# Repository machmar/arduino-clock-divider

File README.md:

# arduino-clock-divider
A clock divider that uses a arduino. It divides by 1; 2; 3; 4; 5; 6; 7; 8; 9 and 10.
```
Animations: (only some versions have this feature - the 1.1.1 and 1.4.1 dont have it for sure and Im not sure about the other versions)
       1.Activate them by unplugging the clock source.
       2.Use the divide by 10 as a clock input for animations.
       3.To select animations, Send a trigger to the divide by 9 pin.
       4.All of the animations are displayed on the divide by 1 to 8 leds
       5.Even thought it is displaying animations, it is still sending gates.
       6.To get back to dividing, just plug the clock jack back in.
```
THIS DIVIDER WILL NOT WORK WITH STEREO CABLES, as it relies on the fact that the mono jack shorts the second terminal of the stereo jack to ground. So If you want to make it work with stereo cables, than you have to connect the second contact to ground on the other side of the cable.

TO MAKE THIS WORK WITH STEREO CABLES, you just need to connect pin A0 to ground. That way the arduino will think you have a jack connected all the time, thus not deploing any animations at all. A optional thing you can do is to add a switch to the A0 that swithecs between 5 and 0 Volts.

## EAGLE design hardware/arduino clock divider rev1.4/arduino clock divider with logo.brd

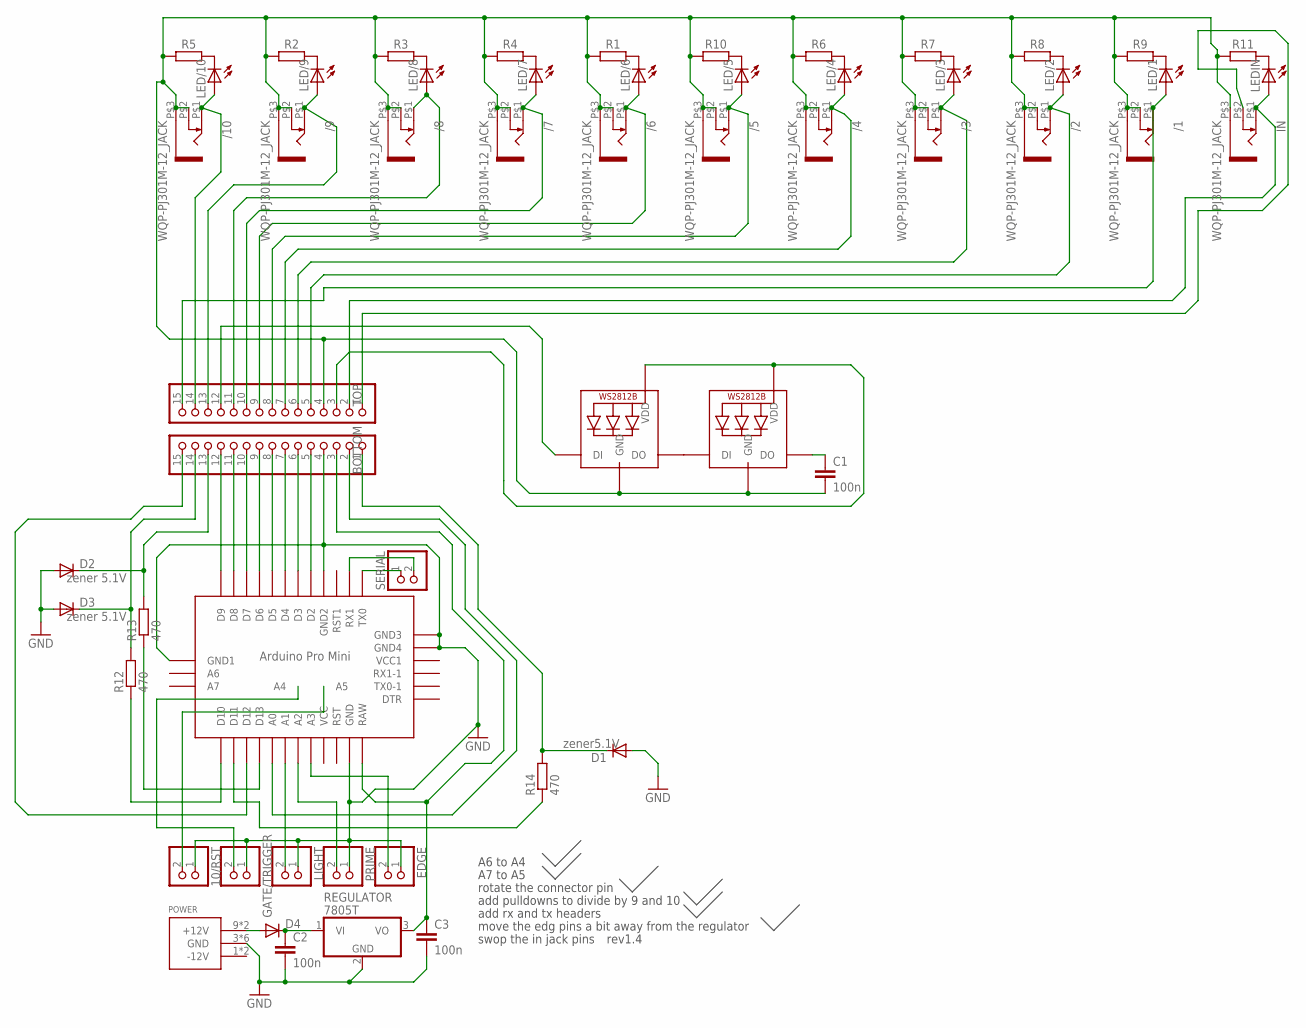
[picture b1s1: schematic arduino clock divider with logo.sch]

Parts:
10/RST: PINHD-1X2; 1X02
/1, /2, /3, /4, /5, /6, /7, /8, /9, /10: WQP-PJ301M-12_JACK
BOTTOM: PINHD-1X15-CB; 1X15-CB3D
C1, C2, C3: 100n; C025-025X050
D1: zener5.1V; DO35-10
D2, D3: zener 5.1V; DO35-10
D4: BAV21; DO35-10
EDGE: PINHD-1X2; 1X02
GATE/TRIGGER: PINHD-1X2; 1X02
IN: WQP-PJ301M-12_JACK
LED/1, LED/2, LED/3, LED/4, LED/5, LED/6, LED/7, LED/8, LED/9, LED/10: LED3MM
LEDIN: LED3MM
LIGHT: PINHD-1X2; 1X02
NEOPIX1, NEOPIX2: WS2812B5050; WS2812B
POWER: POWER_SIMPLE10; POWER_10
PRIME: PINHD-1X2; 1X02
R1, R2, R3, R4, R5, R6, R7, R8, R9, R10: 1k; 0204V
R11: 330; 0204V
R12, R13, R14: 470; 0204/7
REGULATOR: 7805T; TO220H
SERIAL: PINHD-1X2; 1X02
TOP: PINHD-1X15-CB; 1X15-CB3D
U$1: ABK-PRO-MINI-SMD

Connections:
GND: 10/RST.1, BOTTOM.4, C2.2, C3.2, D1.A, D2.A, D3.A, EDGE.1, GATE/TRIGGER.1, LIGHT.1, POWER.3 (GND), POWER.4 (GND), POWER.5 (GND), POWER.6 (GND), POWER.7 (GND), POWER.8 (GND), PRIME.1, REGULATOR.2 (GND), U$1.GND, U$1.GND1, U$1.GND2, U$1.GND3, U$1.GND4
unnamed: /6.P$1 (2), LED/6.A, TOP.9
unnamed: LED/6.K (C), R1.2
unnamed: BOTTOM.13, D2.C, R13.2
unnamed: LED/9.K (C), R2.2
unnamed: /8.P$1 (2), LED/8.A, TOP.11
unnamed: LED/8.K (C), R3.2
unnamed: /5.P$1 (2), LED/5.A, TOP.8
unnamed: LED/7.K (C), R4.2
unnamed: BOTTOM.14, D3.C, R12.2
unnamed: LED/10.K (C), R5.2
unnamed: /4.P$1 (2), LED/4.A, TOP.7
unnamed: LED/4.K (C), R6.2
unnamed: /3.P$1 (2), LED/3.A, TOP.6
unnamed: LED/3.K (C), R7.2
unnamed: /2.P$1 (2), LED/2.A, TOP.5
unnamed: LED/2.K (C), R8.2
unnamed: D4.A, POWER.9 (+12V), POWER.10 (+12V)
unnamed: LED/1.K (C), R9.2
unnamed: C2.1, D4.C, REGULATOR.1 (VI)
unnamed: LED/5.K (C), R10.2
unnamed: R14.1, U$1.D11
unnamed: LEDIN.K (C), R11.2
unnamed: IN.P$2 (3), TOP.1
unnamed: NEOPIX1.4-DIN (DI), TOP.12
unnamed: /7.P$1 (2), LED/7.A, TOP.10
unnamed: NEOPIX1.2-DOUT (DO), NEOPIX2.4-DIN (DI)
unnamed: /10.P$1 (2), LED/10.A, TOP.14
unnamed: C1.1, NEOPIX2.2-DOUT (DO)
unnamed: /9.P$1 (2), LED/9.A, TOP.13
unnamed: NEOPIX1.1-VDD (VDD), NEOPIX2.1-VDD (VDD), TOP.3
unnamed: PRIME.2, U$1.A2
unnamed: BOTTOM.3, C3.1, REGULATOR.3 (VO), U$1.RAW
unnamed: BOTTOM.12, U$1.D9
unnamed: BOTTOM.11, U$1.D8
unnamed: BOTTOM.10, U$1.D7
unnamed: BOTTOM.9, U$1.D6
unnamed: BOTTOM.8, U$1.D5
unnamed: BOTTOM.7, U$1.D4
unnamed: BOTTOM.6, U$1.D3
unnamed: BOTTOM.5, U$1.D2
unnamed: R13.1, U$1.D13
unnamed: R12.1, U$1.D10
unnamed: IN.P$1 (2), LEDIN.A, TOP.2
unnamed: /1.P$1 (2), LED/1.A, TOP.15
unnamed: BOTTOM.1, D1.C, R14.2
unnamed: BOTTOM.15, U$1.D12
unnamed: LIGHT.2, U$1.A1
unnamed: BOTTOM.2, U$1.A0
unnamed: EDGE.2, U$1.A3
unnamed: 10/RST.2, U$1.A5
unnamed: GATE/TRIGGER.2, U$1.A4
unnamed: SERIAL.2, U$1.RX1
unnamed: SERIAL.1, U$1.TX0
TOPGND: /1.P$2 (3), /1.P$3 (1), /2.P$2 (3), /2.P$3 (1), /3.P$2 (3), /3.P$3 (1), /4.P$2 (3), /4.P$3 (1), /5.P$2 (3), /5.P$3 (1), /6.P$2 (3), /6.P$3 (1), /7.P$2 (3), /7.P$3 (1), /8.P$2 (3), /8.P$3 (1), /9.P$2 (3), /9.P$3 (1), /10.P$2 (3), /10.P$3 (1), C1.2, IN.P$3 (1), NEOPIX1.3-GND (GND), NEOPIX2.3-GND (GND), R1.1, R2.1, R3.1, R4.1, R5.1, R6.1, R7.1, R8.1, R9.1, R10.1, R11.1, TOP.4

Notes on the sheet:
A6 to A4
A7 to A5
rotate the connector pin
add pulldowns to divide by 9 and 10
add rx and tx headers
move the edg pins a bit away from the regulator
swop the in jack pins
rev1.4

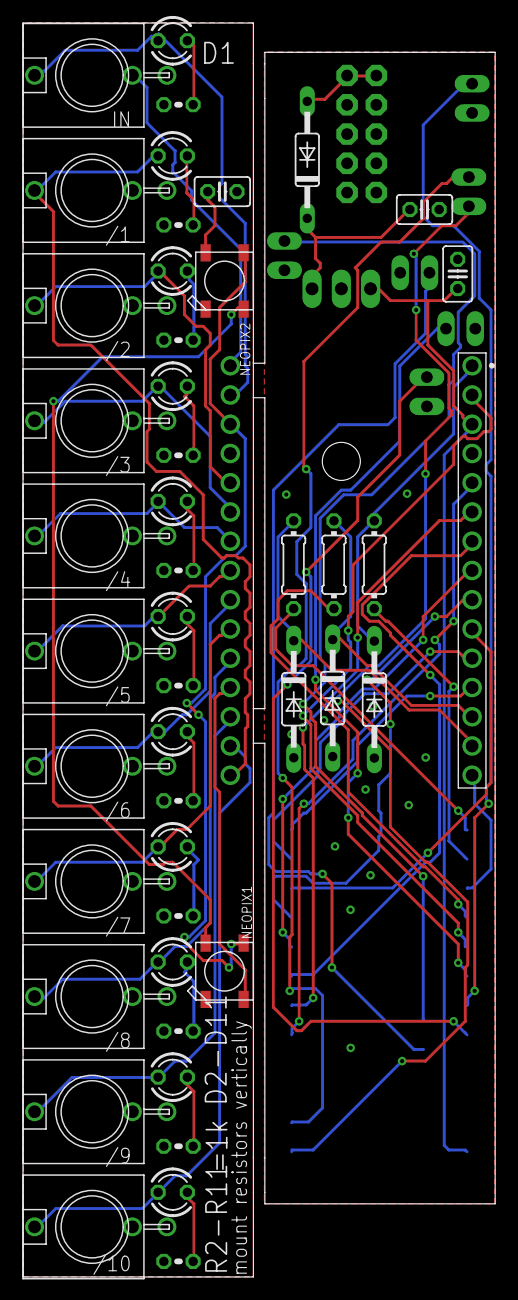
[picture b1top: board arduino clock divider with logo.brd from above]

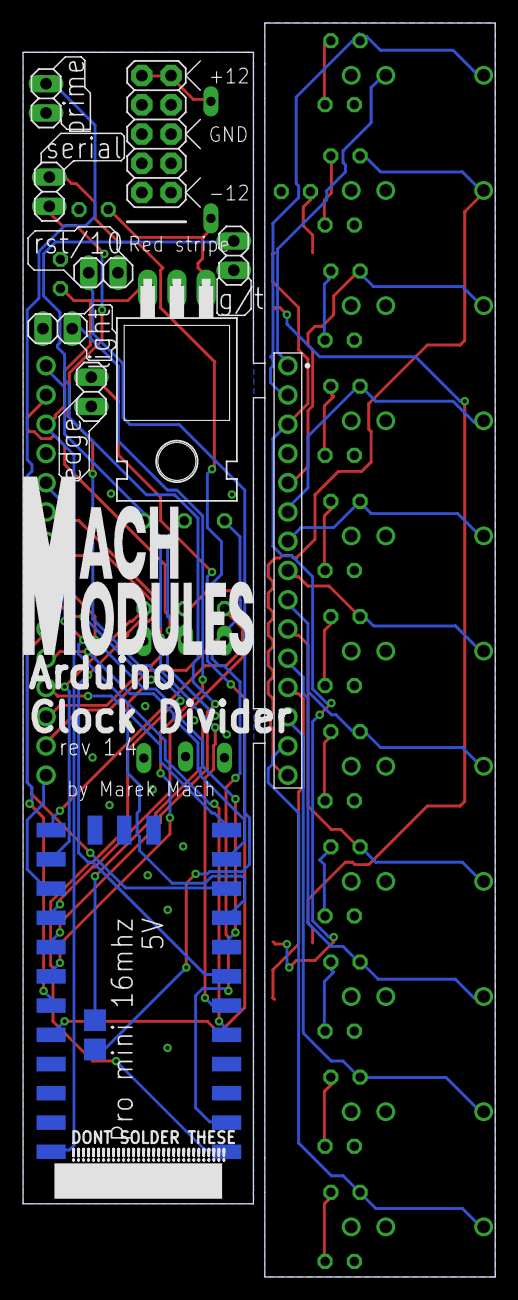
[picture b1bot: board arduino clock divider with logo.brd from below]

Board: 2 copper layers, 41.0 x 108.9 mm, 56 parts (10 on the bottom side), 55 nets.

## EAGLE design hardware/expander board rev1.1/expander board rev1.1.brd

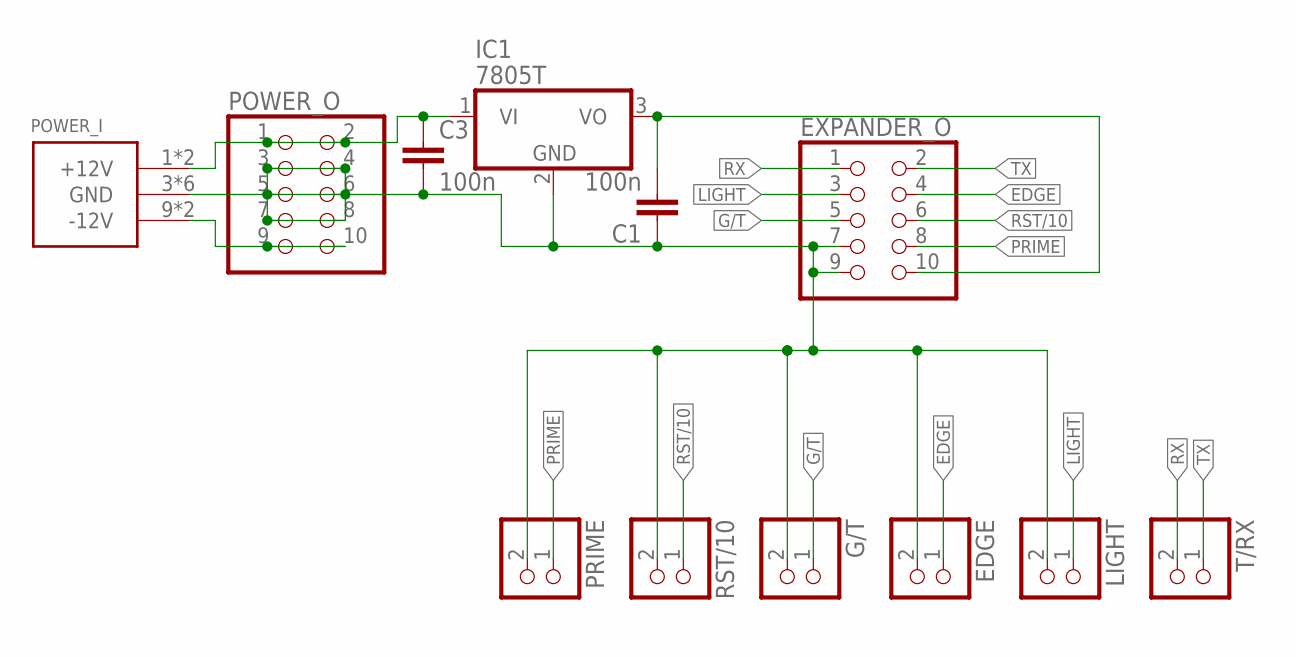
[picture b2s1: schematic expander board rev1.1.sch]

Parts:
C1, C3: 100n; C025-025X050
EDGE: PINHD-1X2; 1X02
EXPANDER_O: PINHD-2X5; 2X05
G/T: PINHD-1X2; 1X02
IC1: 7805T; TO220H
LIGHT: PINHD-1X2; 1X02
POWER_I: POWER_SIMPLE; POWER_10_NSTRIPE
POWER_O: PINHD-2X5; 2X05
PRIME: PINHD-1X2; 1X02
RST/10: PINHD-1X2; 1X02
T/RX: PINHD-1X2; 1X02

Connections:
+5V: C1.2, EXPANDER_O.10, IC1.3 (VO)
+12V: C3.1, IC1.1 (VI), POWER_I.1 (+12V), POWER_I.2 (+12V), POWER_O.1, POWER_O.2
-12V: POWER_I.9 (-12V), POWER_I.10 (-12V), POWER_O.9, POWER_O.10
EDGE: EDGE.1, EXPANDER_O.4
G/T: EXPANDER_O.5, G/T.1
GND: C1.1, C3.2, EDGE.2, EXPANDER_O.7, EXPANDER_O.9, G/T.2, IC1.2 (GND), LIGHT.2, POWER_I.3 (GND), POWER_I.4 (GND), POWER_I.5 (GND), POWER_I.6 (GND), POWER_I.7 (GND), POWER_I.8 (GND), POWER_O.3, POWER_O.4, POWER_O.5, POWER_O.6, POWER_O.7, POWER_O.8, PRIME.2, RST/10.2
LIGHT: EXPANDER_O.3, LIGHT.1
PRIME: EXPANDER_O.8, PRIME.1
RST/10: EXPANDER_O.6, RST/10.1
RX: EXPANDER_O.1, T/RX.2
TX: EXPANDER_O.2, T/RX.1

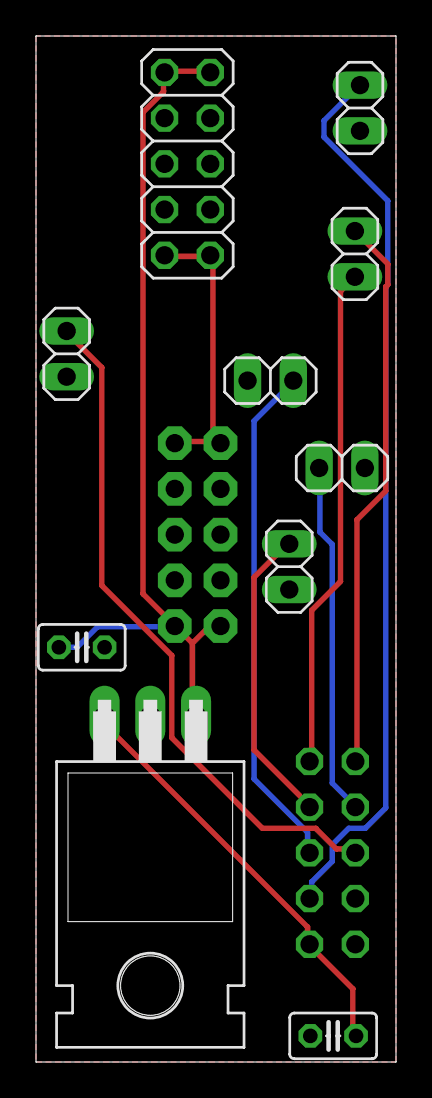
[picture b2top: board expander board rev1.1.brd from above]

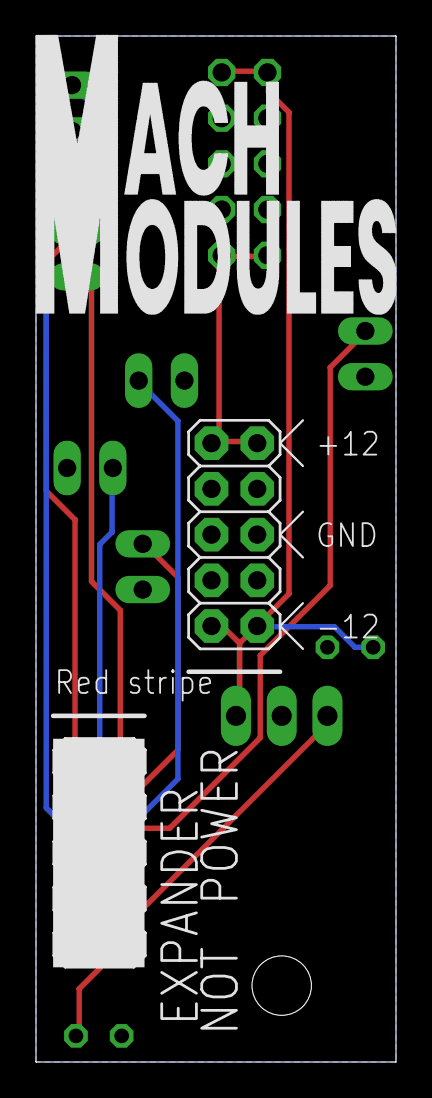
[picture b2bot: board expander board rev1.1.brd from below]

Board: 2 copper layers, 20.0 x 57.0 mm, 12 parts (2 on the bottom side), 11 nets.

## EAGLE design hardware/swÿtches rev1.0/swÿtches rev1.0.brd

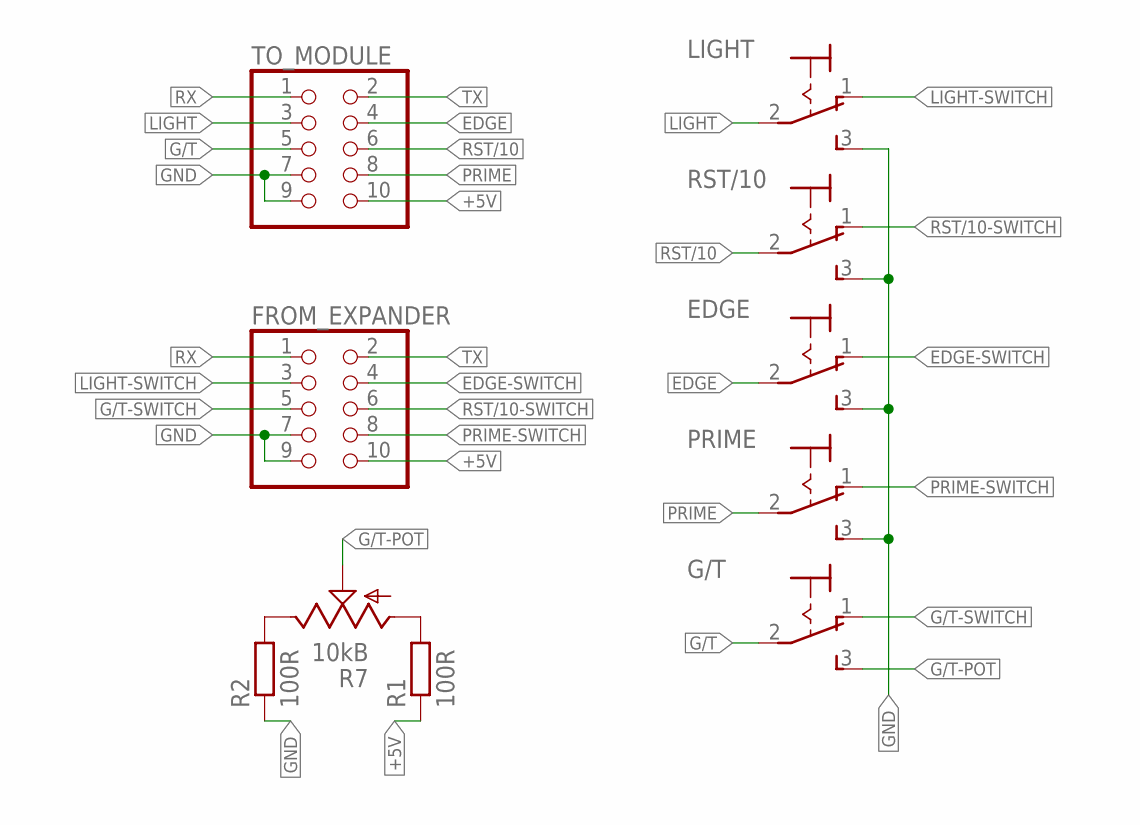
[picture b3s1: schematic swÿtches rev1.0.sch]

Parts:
EDGE: 320-916320-916BIG; 320-916MY
FROM_EXPANDER: PINHD-2X5; 2X05
G/T: 320-916320-916BIG; 320-916MY
LIGHT: 320-916320-916BIG; 320-916MY
PRIME: 320-916320-916BIG; 320-916MY
R1, R2: 100R; 0204/7
R7: 10kB; ALPS_POT_VERTICAL_PS
RST/10: 320-916320-916BIG; 320-916MY
TO_MODULE: PINHD-2X5; 2X05

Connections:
+5V: FROM_EXPANDER.10, R1.1, TO_MODULE.10
EDGE: EDGE.2, TO_MODULE.4
EDGE-SWITCH: EDGE.1 (O), FROM_EXPANDER.4
G/T: G/T.2, TO_MODULE.5
G/T-POT: G/T.3 (S), R7.P$2 (S)
G/T-SWITCH: FROM_EXPANDER.5, G/T.1 (O)
GND: EDGE.3 (S), FROM_EXPANDER.7, FROM_EXPANDER.9, LIGHT.3 (S), PRIME.3 (S), R2.1, RST/10.3 (S), TO_MODULE.7, TO_MODULE.9
LIGHT: LIGHT.2, TO_MODULE.3
LIGHT-SWITCH: FROM_EXPANDER.3, LIGHT.1 (O)
unnamed: R2.2, R7.P$1 (E)
unnamed: R1.2, R7.P$3 (A)
PRIME: PRIME.2, TO_MODULE.8
PRIME-SWITCH: FROM_EXPANDER.8, PRIME.1 (O)
RST/10: RST/10.2, TO_MODULE.6
RST/10-SWITCH: FROM_EXPANDER.6, RST/10.1 (O)
RX: FROM_EXPANDER.1, TO_MODULE.1
TX: FROM_EXPANDER.2, TO_MODULE.2

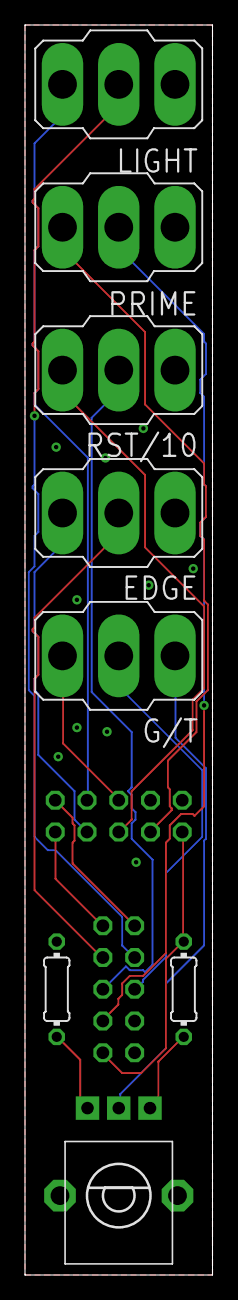
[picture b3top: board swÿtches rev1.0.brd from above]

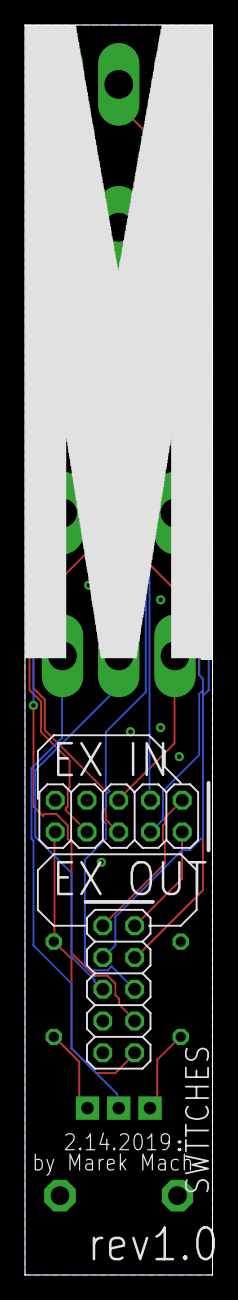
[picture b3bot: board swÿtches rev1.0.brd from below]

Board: 2 copper layers, 15.0 x 100.0 mm, 10 parts (2 on the bottom side), 17 nets.

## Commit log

2018-10-06 A new update
    I have added animations.
2018-12-21 Animtions finished
    (for some reason the 9jack stopped working
2018-12-21 and the schematic changet a little bit
2019-07-30 updated library descriptions
2019-07-30 newer revisions
2019-07-30 added new hardware files
2020-08-28 new code for the first design prototype
2020-08-28 added readme description
2020-09-11 complete code rework
2020-09-11 Added an extensive README
2020-09-12 updated expander description
2020-09-12 added and fixed hardware designs
2020-09-12 edited expander warning thing
2020-09-12 fixed a small boot bug
2020-09-13 added LEDs description switch
